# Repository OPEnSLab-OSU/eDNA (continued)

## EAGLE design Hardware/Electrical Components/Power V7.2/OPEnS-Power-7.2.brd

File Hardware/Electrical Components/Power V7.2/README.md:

# 12V Version 7.2
Power Control Board for microcontroller projects, designed at OPEnS Lab OSU.

The board use a [D-Flipflop](https://www.digikey.com/product-detail/en/texas-instruments/SN74LVC1G175DBVR/296-17617-1-ND/706599) to store the current state of the system.

| D-Flipflop     |
|:-------------:|
|  |

| Schematic Name | Pin Name                  |
|----------------|---------------------------|
| `Q`            | Input - tied HIGH         |
| `D`            | Output to power regulator |
| `CLK`          | Clock                     |
| `!CLR`         | Clear - Reset             |

The flipflop IC is work based on raising, positive edge of the clock (posedge)
The input `D` is always tied HIGH.
The `CLK` is normally pulled low until triggered by the Feather.

> In the original sleep state:
 * `D` is HIGH
 * `Q` is HIGH
 * `CLK` is LOW
 * `CLR` is HIGH

> when the RTC fires the alarm:

`CLR` (reset) is pulled down to GND -> make the output `Q` LOW
		-> Turn on the power regulator. The state remain the same since there is no change in the clock
		
> When Feather fired the shutdown signal:

`CLK` (reset) goes low->high which copy the input `D` to the output `Q`. Since `D` is always high,
		the output `Q` will change to HIGH -> shutdown the voltage regulator

System stay as sleep until the RTC fires again -> reset the flipflop

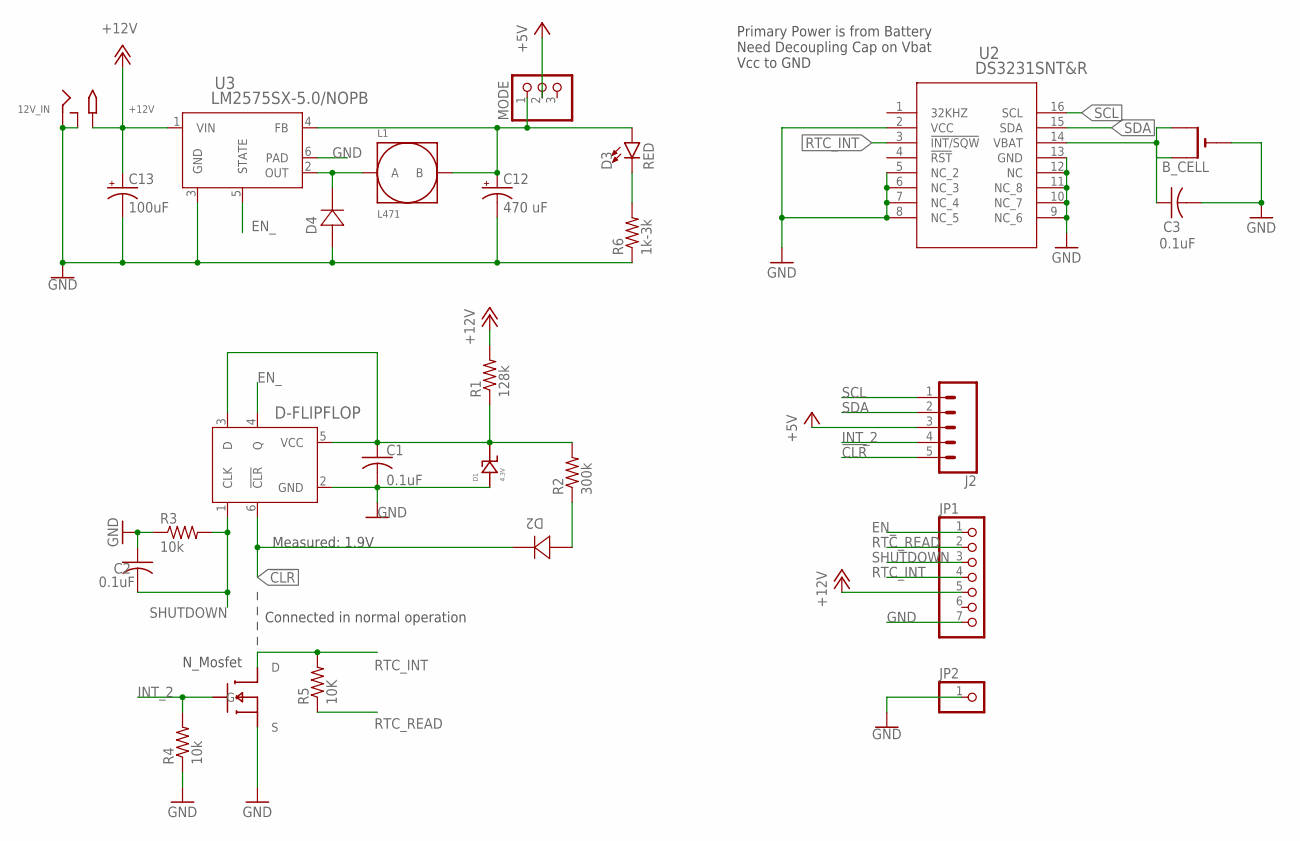
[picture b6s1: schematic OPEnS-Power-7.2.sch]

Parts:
12V_IN: 2.1MMJACKSMT; DCJACK_2MM_SMT
B_CELL: CR1220SMT; CR1220-SMD
C1, C2, C3: 0.1uF; C1206
C12: 470 uF; 153CLV-0810
C13: 100uF; 153CLV-0505
D1: 4.3V; DO-219AC
D2, D4: S1A-13-F; SMA
D3: RED; LED-1206
D-FLIPFLOP: SN74LVC1G175DBVR; DBV6
J2: CONN_05; 1X05
JP1: PINHD-1X7; 1X07
JP2: PINHD-1X1; 1X01
L1: L471; 12-12
MODE: PINHD-1X3; 1X03
MOSFET: MOSFET-SOT23F; SOT-23F
R1: 128k; R1206
R2: 300k; R1206
R3, R4: 10k; R1206
R5: 10K; R1206
R6: 1k-3k; R1206
U2: DS3231SNT&R; 21-0042B_16
U3: LM2575SX-5.0/NOPB; KTT0005B

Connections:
5_RAW: C12.+, D3.A, L1.B, MODE.1, U3.4 (FB)
!CLR: D2.1, D-FLIPFLOP.6 (!CLR), J2.5
+5V: J2.3, MODE.2
+12V: 12V_IN.PWR2 (TIP), C13.+, JP1.5, R1.2, U3.1 (VIN)
EN_: D-FLIPFLOP.4 (Q), JP1.1, U3.5 (STATE)
GND: 12V_IN.GND (RING), 12V_IN.GNDBREAK (RING_SW), B_CELL.-, C1.2, C2.1, C3.2, C12.-, C13.-, D1.BCK, D4.2, D-FLIPFLOP.2 (GND), JP1.7, JP2.1, MOSFET.S, R3.1, R4.1, R6.1, U2.2 (VCC), U2.5 (NC_2), U2.6 (NC_3), U2.7 (NC_4), U2.8 (NC_5), U2.9 (NC_6), U2.10 (NC_7), U2.11 (NC_8), U2.12 (NC), U2.13 (GND), U3.3 (GND), U3.6 (PAD); also elsewhere on the board
INT_2: J2.4, MOSFET.G, R4.2
unnamed: D4.1, L1.A, U3.2 (OUT)
unnamed: C1.1, D1.FNT, D-FLIPFLOP.3 (D), D-FLIPFLOP.5 (VCC), R1.1, R2.2
unnamed: B_CELL.+$1 (+), B_CELL.+$2 (+1), C3.1, U2.14 (VBAT)
unnamed: D2.2, R2.1
unnamed: D3.C, R6.2
RTC_INT: JP1.4, MOSFET.D, R5.2, U2.3 (!INT/SQW); also elsewhere on the board
RTC_READ: JP1.2, R5.1
SCL: J2.1, U2.16 (SCL)
SDA: J2.2, U2.15 (SDA)
SHUTDOWN: C2.2, D-FLIPFLOP.1 (CLK), JP1.3, R3.2

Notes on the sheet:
Measured: 1.9V
Primary Power is from Battery Need Decoupling Cap on Vbat Vcc to GND
Connected in normal operation
N_Mosfet

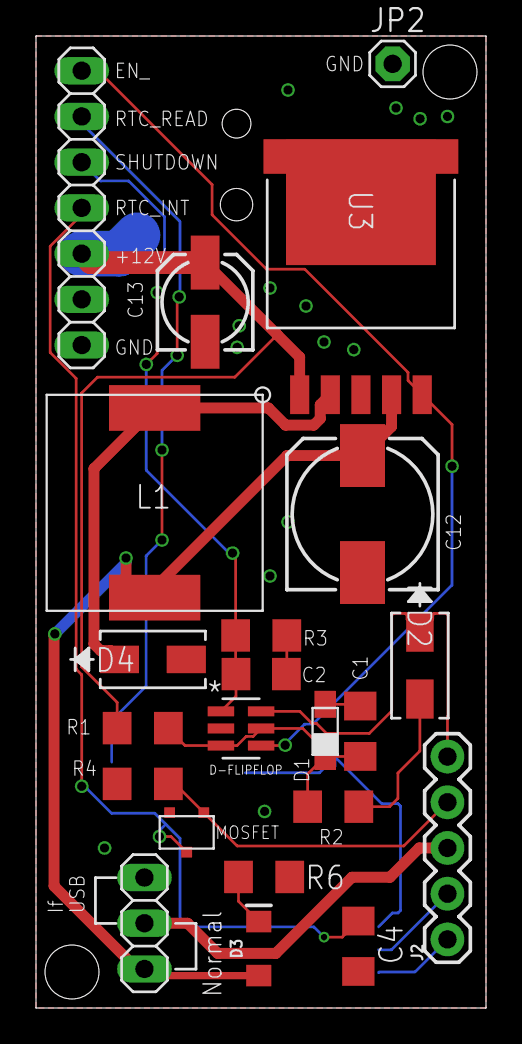
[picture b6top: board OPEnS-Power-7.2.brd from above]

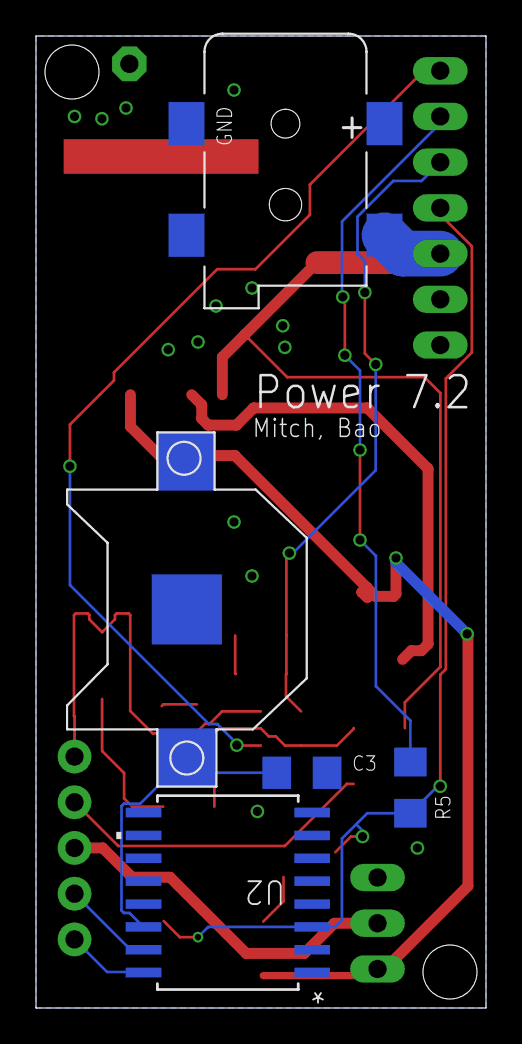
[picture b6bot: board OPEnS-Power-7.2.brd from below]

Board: 2 copper layers, 25.0 x 54.0 mm, 27 parts (5 on the bottom side), 17 nets.

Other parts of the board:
C4: 0.1uF; C1206

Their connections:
GND: C4.2; also elsewhere on the board
RTC_INT: C4.1; also elsewhere on the board

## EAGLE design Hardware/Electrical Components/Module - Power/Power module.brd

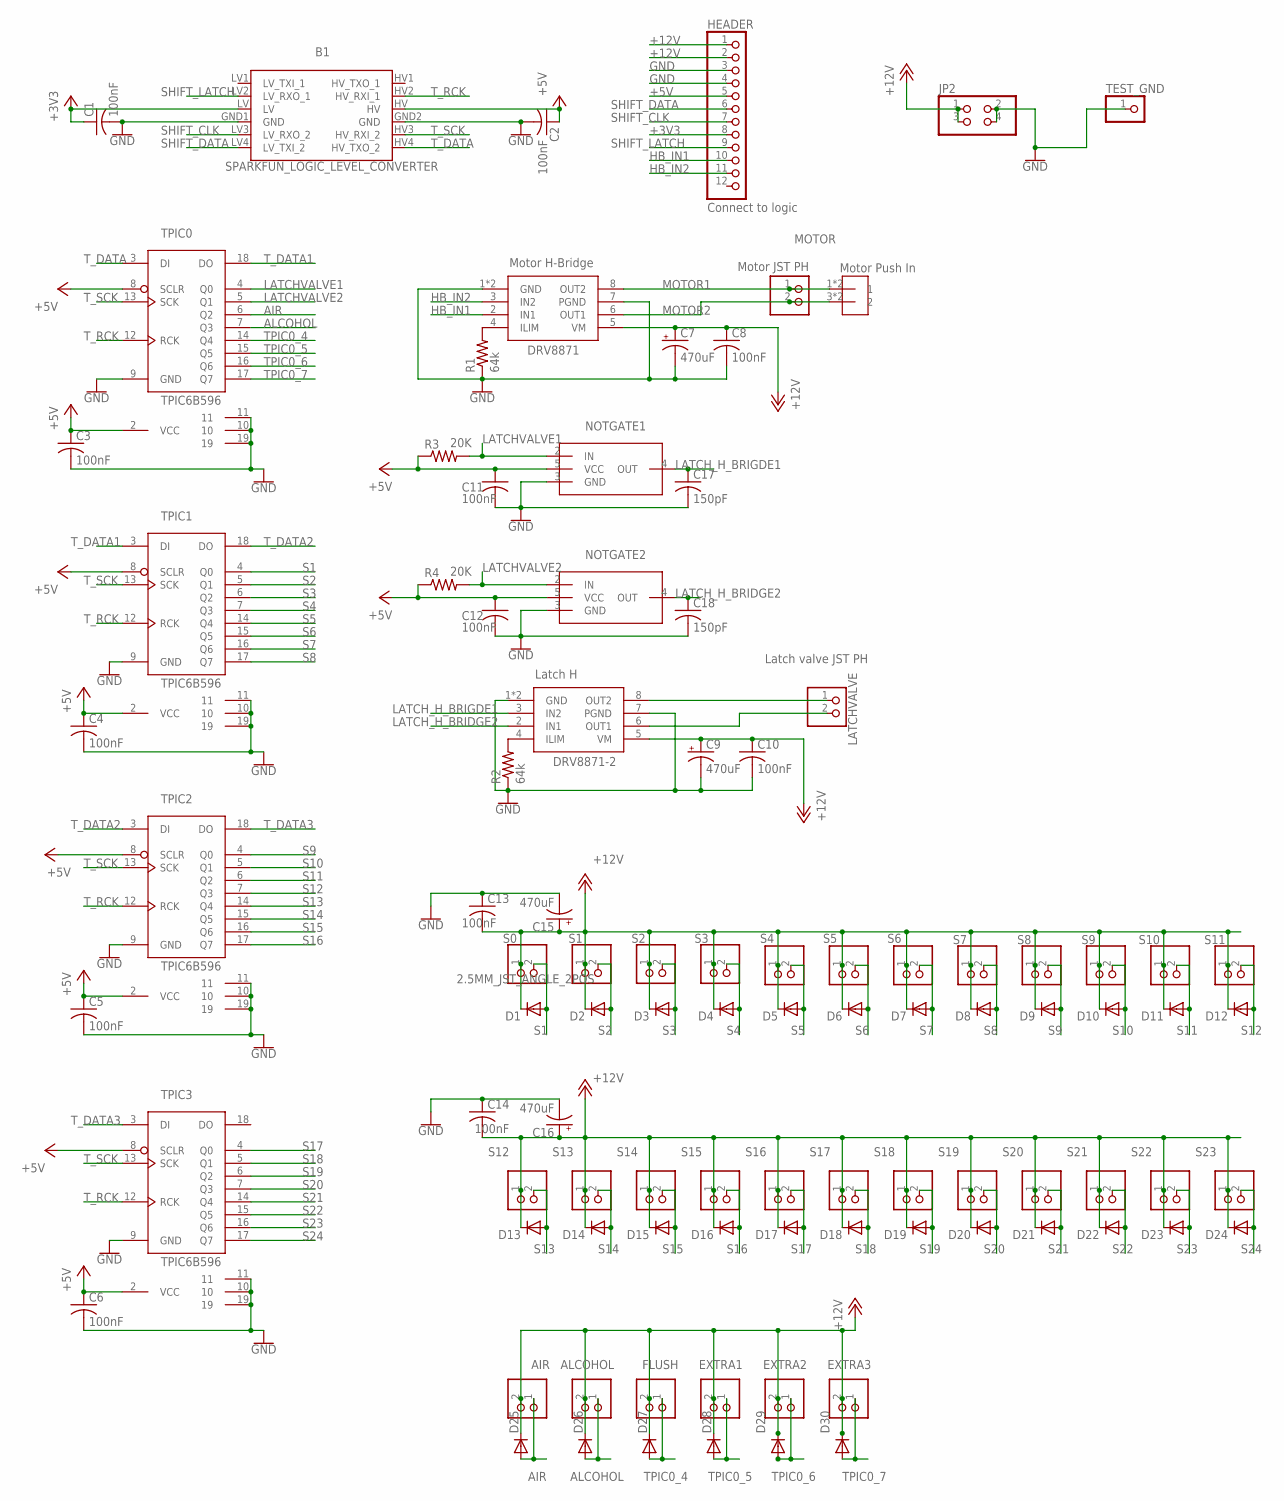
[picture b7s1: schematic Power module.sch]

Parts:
AIR: 2.5MM_JST_UP_2POS; JST_2POS_2.5MM_UP
ALCOHOL: 2.5MM_JST_UP_2POS; JST_2POS_2.5MM_UP
B1: SPARKFUN_LOGIC_LEVEL_CONVERTER
C1, C2, C3, C4, C5, C6, C8, C10, C13, C14: 100nF; C050-024X044
C7, C9, C15, C16: 470uF; 140CLH-0810
C11, C12: 100nF; C1206
C17, C18: 150pF; C050-024X044
D1, D2, D3, D4, D5, D6, D7, D8, D9, D10, D11, D12, D13, D14, D15, D16, D17, D18, D19, D20, D21, D22, D23, D24, D25, D26, D27, D28, D29, D30: DIODESOD-123; SOD-123
DRV8871: Motor H-Bridge; SOP8
DRV8871-2: Latch H; SOP8
EXTRA1, EXTRA2, EXTRA3: 2.5MM_JST_UP_2POS; JST_2POS_2.5MM_UP
FLUSH: 2.5MM_JST_UP_2POS; JST_2POS_2.5MM_UP
HEADER: Connect to logic; 1X12
JP2: PINHD-2X2; 2X02
LATCHVALVE: Latch valve JST PH; JST_2POS_2.5MM_UP
MOTOR: Motor JST PH; JST_2POS_2.5MM_UP
NOTGATE1, NOTGATE2: NOT_GATE; SOT753
R1, R2: 64k; 0204/5
R3, R4: 20K; R1206
S0, S1, S2, S3, S4, S5, S6, S7, S8, S9, S10, S11, S12, S13, S14, S15, S16, S17, S18, S19, S20, S21, S22, S23: 2.5MM_JST_ANGLE_2POS; JST_2POS_2.5MM_ANGLE
TEST_GND: PINHD-1X1; 1X01
TPIC0, TPIC1, TPIC2, TPIC3: TPIC6B596; DIP20
U$1: Motor Push In; 3.5MM_DIP2

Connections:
+3V3: B1.LV, C1.1, HEADER.8
+5V: B1.HV, C2.1, C3.1, C4.1, C5.1, C6.1, C11.1, C12.1, HEADER.5, NOTGATE1.5 (VCC), NOTGATE2.5 (VCC), R3.1, R4.1, TPIC0.2 (VCC), TPIC0.8 (SCLR), TPIC1.2 (VCC), TPIC1.8 (SCLR), TPIC2.2 (VCC), TPIC2.8 (SCLR), TPIC3.2 (VCC), TPIC3.8 (SCLR)
+12V: AIR.2, ALCOHOL.2, C7.+, C8.1, C9.+, C10.1, C13.2, C14.2, C15.+, C16.+, D1.C, D2.C, D3.C, D4.C, D5.C, D6.C, D7.C, D8.C, D9.C, D10.C, D11.C, D12.C, D13.C, D14.C, D15.C, D16.C, D17.C, D18.C, D19.C, D20.C, D21.C, D22.C, D23.C, D24.C, D25.C, D26.C, D27.C, D28.C, D29.C, D30.C, DRV8871.5 (VM), DRV8871-2.5 (VM), EXTRA1.2, EXTRA2.2, EXTRA3.2, FLUSH.2, HEADER.1, HEADER.2, JP2.1, JP2.3, S0.1 (2), S1.1 (2), S2.1 (2), S3.1 (2), S4.1 (2), S5.1 (2), S6.1 (2), S7.1 (2), S8.1 (2), S9.1 (2), S10.1 (2), S11.1 (2), S12.1 (2), S13.1 (2), S14.1 (2), S15.1 (2), S16.1 (2), S17.1 (2), S18.1 (2), S19.1 (2), S20.1 (2), S21.1 (2), S22.1 (2), S23.1 (2)
AIR: AIR.1, D25.A, TPIC0.6 (Q2)
ALCOHOL: ALCOHOL.1, D26.A, TPIC0.7 (Q3)
GND: B1.GND1 (GND), B1.GND2 (GND), C1.2, C2.2, C3.2, C4.2, C5.2, C6.2, C7.-, C8.2, C9.-, C10.2, C11.2, C12.2, C13.1, C14.1, C15.-, C16.-, C17.2, C18.2, DRV8871.1 (GND), DRV8871.7 (PGND), DRV8871.GND, DRV8871-2.1 (GND), DRV8871-2.7 (PGND), DRV8871-2.GND, HEADER.3, HEADER.4, JP2.2, JP2.4, NOTGATE1.3 (GND), NOTGATE2.3 (GND), R1.1, R2.1, TEST_GND.1, TPIC0.9 (GND), TPIC0.10, TPIC0.11, TPIC0.19, TPIC1.9 (GND), TPIC1.10, TPIC1.11, TPIC1.19, TPIC2.9 (GND), TPIC2.10, TPIC2.11, TPIC2.19, TPIC3.9 (GND), TPIC3.10, TPIC3.11, TPIC3.19
HB_IN1: DRV8871.2 (IN1), HEADER.10
HB_IN2: DRV8871.3 (IN2), HEADER.11
LATCHVALVE1: NOTGATE1.2 (IN), R3.2, TPIC0.4 (Q0)
LATCHVALVE2: NOTGATE2.2 (IN), R4.2, TPIC0.5 (Q1)
LATCH_H_BRIDGE2: C18.1, DRV8871-2.2 (IN1), NOTGATE2.4 (OUT)
LATCH_H_BRIGDE1: C17.1, DRV8871-2.3 (IN2), NOTGATE1.4 (OUT)
MOTOR1: DRV8871.8 (OUT2), MOTOR.1, U$1.1, U$1.2 (1)
MOTOR2: DRV8871.6 (OUT1), MOTOR.2, U$1.3 (2), U$1.4 (2)
unnamed: DRV8871-2.4 (ILIM), R2.2
unnamed: DRV8871.4 (ILIM), R1.2
unnamed: DRV8871-2.8 (OUT2), LATCHVALVE.1
unnamed: DRV8871-2.6 (OUT1), LATCHVALVE.2
S1: D1.A, S0.2 (1), TPIC1.4 (Q0)
S2: D2.A, S1.2 (1), TPIC1.5 (Q1)
S3: D3.A, S2.2 (1), TPIC1.6 (Q2)
S4: D4.A, S3.2 (1), TPIC1.7 (Q3)
S5: D5.A, S4.2 (1), TPIC1.14 (Q4)
S6: D6.A, S5.2 (1), TPIC1.15 (Q5)
S7: D7.A, S6.2 (1), TPIC1.16 (Q6)
S8: D8.A, S7.2 (1), TPIC1.17 (Q7)
S9: D9.A, S8.2 (1), TPIC2.4 (Q0)
S10: D10.A, S9.2 (1), TPIC2.5 (Q1)
S11: D11.A, S10.2 (1), TPIC2.6 (Q2)
S12: D12.A, S11.2 (1), TPIC2.7 (Q3)
S13: D13.A, S12.2 (1), TPIC2.14 (Q4)
S14: D14.A, S13.2 (1), TPIC2.15 (Q5)
S15: D15.A, S14.2 (1), TPIC2.16 (Q6)
S16: D16.A, S15.2 (1), TPIC2.17 (Q7)
S17: D17.A, S16.2 (1), TPIC3.4 (Q0)
S18: D18.A, S17.2 (1), TPIC3.5 (Q1)
S19: D19.A, S18.2 (1), TPIC3.6 (Q2)
S20: D20.A, S19.2 (1), TPIC3.7 (Q3)
S21: D21.A, S20.2 (1), TPIC3.14 (Q4)
S22: D22.A, S21.2 (1), TPIC3.15 (Q5)
S23: D23.A, S22.2 (1), TPIC3.16 (Q6)
S24: D24.A, S23.2 (1), TPIC3.17 (Q7)
SHIFT_CLK: B1.LV3 (LV_RXO_2), HEADER.7
SHIFT_DATA: B1.LV4 (LV_TXI_2), HEADER.6
SHIFT_LATCH: B1.LV2 (LV_RXO_1), HEADER.9
TPIC0_4: D27.A, FLUSH.1, TPIC0.14 (Q4)
TPIC0_5: D28.A, EXTRA1.1, TPIC0.15 (Q5)
TPIC0_6: D29.A, EXTRA2.1, TPIC0.16 (Q6)
TPIC0_7: D30.A, EXTRA3.1, TPIC0.17 (Q7)
T_DATA: B1.HV4 (HV_TXO_2), TPIC0.3 (DI)
T_DATA1: TPIC0.18 (DO), TPIC1.3 (DI)
T_DATA2: TPIC1.18 (DO), TPIC2.3 (DI)
T_DATA3: TPIC2.18 (DO), TPIC3.3 (DI)
T_RCK: B1.HV2 (HV_RXI_1), TPIC0.12 (RCK), TPIC1.12 (RCK), TPIC2.12 (RCK), TPIC3.12 (RCK)
T_SCK: B1.HV3 (HV_RXI_2), TPIC0.13 (SCK), TPIC1.13 (SCK), TPIC2.13 (SCK), TPIC3.13 (SCK)

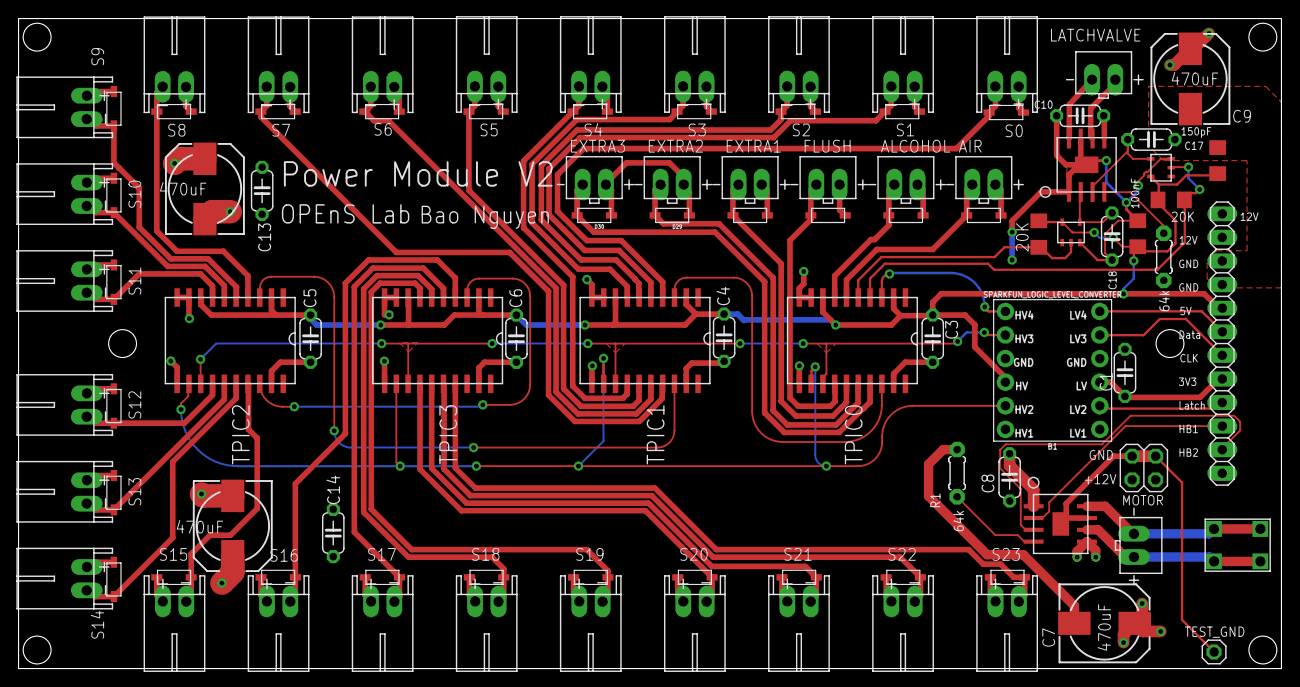
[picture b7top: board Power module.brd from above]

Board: 2 copper layers, 136.0 x 70.0 mm, 96 parts (0 on the bottom side), 55 nets.

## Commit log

2019-05-25 Initial Publication
    eDNA framework derived from OPEnSampler Framework including support for:
    - System-Components Design Pattern
    - Async Task Scheduling
    - State Machine
    Added Components:
    - Web Server with callback support
2019-05-25 Added ArduinoSSC Library
2019-06-08 Added a bunch of functionalities
    + RTC time keeping
    + Power management
    + JSON APIs using ArduinoJSON
    + Simplified shift register APIs
    o Bug fixes
    - Action.hpp
2019-07-09 Hardware Integration
    + Added hardware folder
    + Added software folder
    O Moved software stuff to the its own folder
2019-07-09 A very very big update
    New Features:
    + State Machine
    + SD card logging and storage
    + Ability to set UTC time via the web interface
    + Status
    + RTC time setting and interrupt
2019-07-11 First Hardware Update
    +Add BOM, schematic, PCB for: Power Module, Logic Module, Sensor Module, Depth Sensor, Inline Pressure Sensor, Flow Sensor.
    +Add library + example code for Depth Sensor (MS5803-02BA): MS5803-02.zip
    +Add basic I2C arduino code for Flow Sensor: flowsensor.ino
2019-07-20 Clarify text in PCBs
    O Add text for 3PDT Switch breakout board better PCB annotation
    O Rename MOSFET that controls LED for Programming Mode -> P_MOS
    + Add JST Male to BOM Logic Module – Power V8
    O Correct excel formula for a total price of Logic Module
2019-07-20 Changing deep sleep power board to v7.2
    + Add OpenSPower V7.2: bugs fixed from version v7.1. Now stable under motor noise.
    + Add Logic Module V2 – Power V7.2: Apply new change in PCB to work with OpenSPower V7.2. The 5V voltage regulator is now in the OpenSPower board instead of on the Power Module. Switch pins are also 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
    - Remove power N-type MOSFET that controls power for Power Module V2 since power consumption in idle without MOSFET is suitable with the battery.
2019-07-26 Major fix for sensor module
    O Power Module: Changes in footprint location of motor push-to-connect for mounting place. Move the 90-angle header further inside for better mechanical support
    O Sensor Module: Rearrange 2.5mm headphone jack closer to the edge for proper mounting. The older version stops the male jack fully dock with the female casing thus fail to connect. Move the 90-angle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
    O MS5803-02BA: Change symbol, change SDA -> SDO. This label caused the PCB to stop working with all I2C devices. Sensor Module: Rewire to the write SDA, tested.
    + Add MS5803-02BA Datasheet
2019-08-11 Bug fix for Powerboard 7.2V
    Changed R5 and R2 value to protect against RTC_READ floating when feather is as sleep.
    Added C4 capacitor to further protect against floating RTC_READ.
2019-08-31 Remove OpenSPower V8
    This powerboard version did not function. Tested V7.2 is stable
2019-09-04 Web Interface 2.0
    New Features:
    + Integration of flow, barometric, and depth sensors
    + Much improved three-stages decontamination procedure
    + Ability to detect programming/normal operation
    Modifications:
    + Renamed classes and further simplification of the codebase
2019-09-04 Commit Web FIles
2019-09-04 Updates
    Updated eDNA Eagle Library
    Update OpenSPower7.2 BOM
    Add OpenSPower 7.2 ReadMe
    Add picture for FlowSensor
    General clean up
2019-11-26 Update BOM Sensor module.xlsx
    Change 2.5mm audio jack from Reel to Cut Tape
2020-02-11 First draft for Logic Module V3
    Combine Power V7.3 with Logic Module
2020-02-11 Updated documentation for Logic Module V3, includes BOM, board pdf, gerber files, .sch and .brd files for Logic Module and 2PDT Switch.
2020-02-11 Newest version of Logic Module V3
2020-02-19 Empty Trash
2020-02-19 Initial Commit (Interface)
2020-02-19 Fixed Emotion CSS Props not working correctly
2020-02-20 Added MUI SASS Starter Code
    + CSS and SASS loaders
    + Emotion babel plugin
2020-02-21 Added components for build TaskConfig
    + Headline
    + TextArea
    + TextField
2020-02-22 Added Formik form control
2020-02-22 (Server) Added ability to reset valve arrays to config file
2020-02-22 Added filtering function in ValveManager and fixed and explicite (char *) cast to char[] for Json Encoding
2020-02-22 Added AppContext and RightBar
2020-08-28 Add Flow Sensor 2 Board
    Incomplete
2023-05-31 File/Folder Re-organization
2023-07-21 Updated README.md
    Replaced old V2 Sampler Images with V4 Sampler Images
2023-10-15 File Organization
2023-10-15 Uploading documents
2023-10-15 Updating Abstract
2023-10-23 Updated Abstract and created HIC
2023-10-23 Update HardwareX Files
2023-10-30 Updated HardwareX Drafts
    Finished draft 1 of "Hardware in Context" Section
    Created draft document for "Hardware Description" Section
2023-10-30 Update HardwareX Organization
    Created a dedicated forlder for section Drafts.
    Included Godshalk's Review Reference File
2023-11-10 Updated Hardware Description
2023-11-14 Updated HardwareX
2023-12-03 Updated HardwareX "HD" section
2023-12-09 Updated Hardware Descript
    Added Electronics Block Diagram
2023-12-15 Created .tex for HardwareX
2023-12-16 Updated HardwareX LaTeX
2023-12-22 Update HardwareX LaTeX
2023-12-29 HardwareX LaTeX
2024-01-03 Upload PolyWAG EDA FIles
2024-01-03 Upload EDA FIles
2024-01-03 Upload CAD - Full Assembly
2024-01-03 Update HardwareX
2024-01-10 Update HardwareX
    Minor Changes to the main page
    Started working on the Design Files Table
2024-01-10 Remove unneeded lLaTeX files
2024-01-26 Update HardwareX
    Added Nathan's Section draft to the HardwareX LaTeX File
2024-01-26 Upload Current Sampler Code
    Uploaded the Sampler UI and Server code. Framework code still needs to be uploaded
2024-01-27 Upload Sampler Code
    Uploaded Sampler UI and Server Code there may be some issues with the addition of the Framework
2024-01-27 Uploaded CAD Files
    Uploaded all of the CAD files from Fusion 360
2024-01-27 Fixing Submodule Issue
2024-01-27 Upload Sampler Code
    Uploaded Sampler UI, Server, and Framework Code
2024-02-01 Add README.md
    Add a README for the LaTeX for basic environment setup tips for new users
2024-02-01 Update LaTeX
2024-02-09 Update HardwareX Paper
2024-02-17 Removed Unnecessary Files
2024-02-19 Remove unneccessary LaTeX Files
2024-02-19 misc
2024-02-20 added the new conclusion
2024-02-27 took out rikey's orchid because it might be caisng formating issues with zenodo
2024-02-27 Update .zenodo.json, added upload type and publication
2024-02-27 added UI-pictures
2024-08-27 Update .zenodo.json
    Added the names of the people that wrote the build guide.
2024-12-13 Add files via upload
    eDNA bill of material
